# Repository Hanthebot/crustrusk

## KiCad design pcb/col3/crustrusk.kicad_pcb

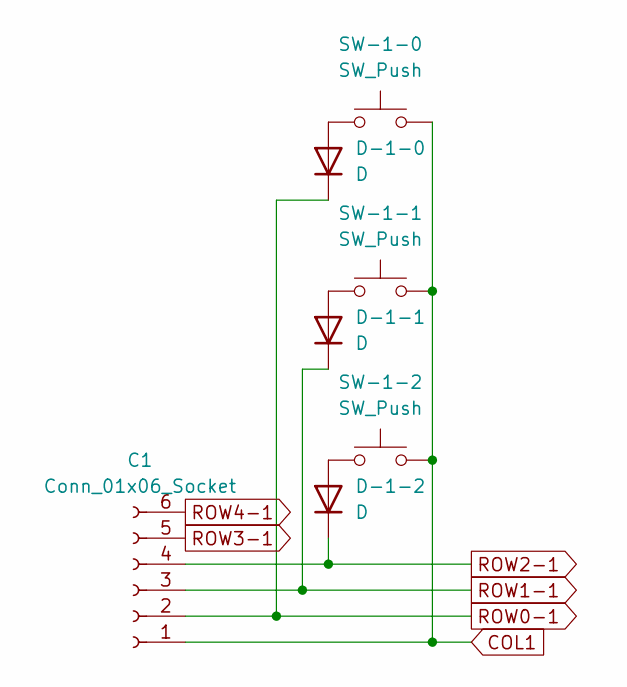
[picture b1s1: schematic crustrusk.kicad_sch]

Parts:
C1: Conn_01x06_Socket; JST_PH_S6B-PH-K_1x06_P2.00mm_Horizontal
D-1-0, D-1-1, D-1-2: D; Diode_TH_SMD_REVERSIBLE
SW-1-0, SW-1-1, SW-1-2: SW_Push; Kailh_socket_MX

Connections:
COL1: C1.1, SW-1-0.2, SW-1-1.2, SW-1-2.2
unnamed: D-1-0.2 (A), SW-1-0.1
unnamed: D-1-1.2 (A), SW-1-1.1
unnamed: D-1-2.2 (A), SW-1-2.1
ROW0-1: C1.2, D-1-0.1 (K)
ROW1-1: C1.3, D-1-1.1 (K)
ROW2-1: C1.4, D-1-2.1 (K)
ROW3-1: C1.5
ROW4-1: C1.6

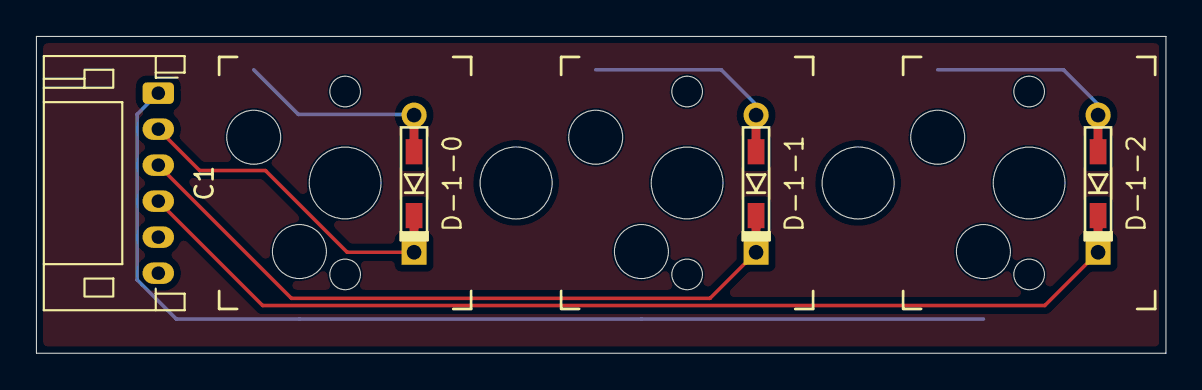
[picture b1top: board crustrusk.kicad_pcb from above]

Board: 2 copper layers, 62.8 x 17.6 mm, 7 parts (0 on the bottom side), 7 nets.
